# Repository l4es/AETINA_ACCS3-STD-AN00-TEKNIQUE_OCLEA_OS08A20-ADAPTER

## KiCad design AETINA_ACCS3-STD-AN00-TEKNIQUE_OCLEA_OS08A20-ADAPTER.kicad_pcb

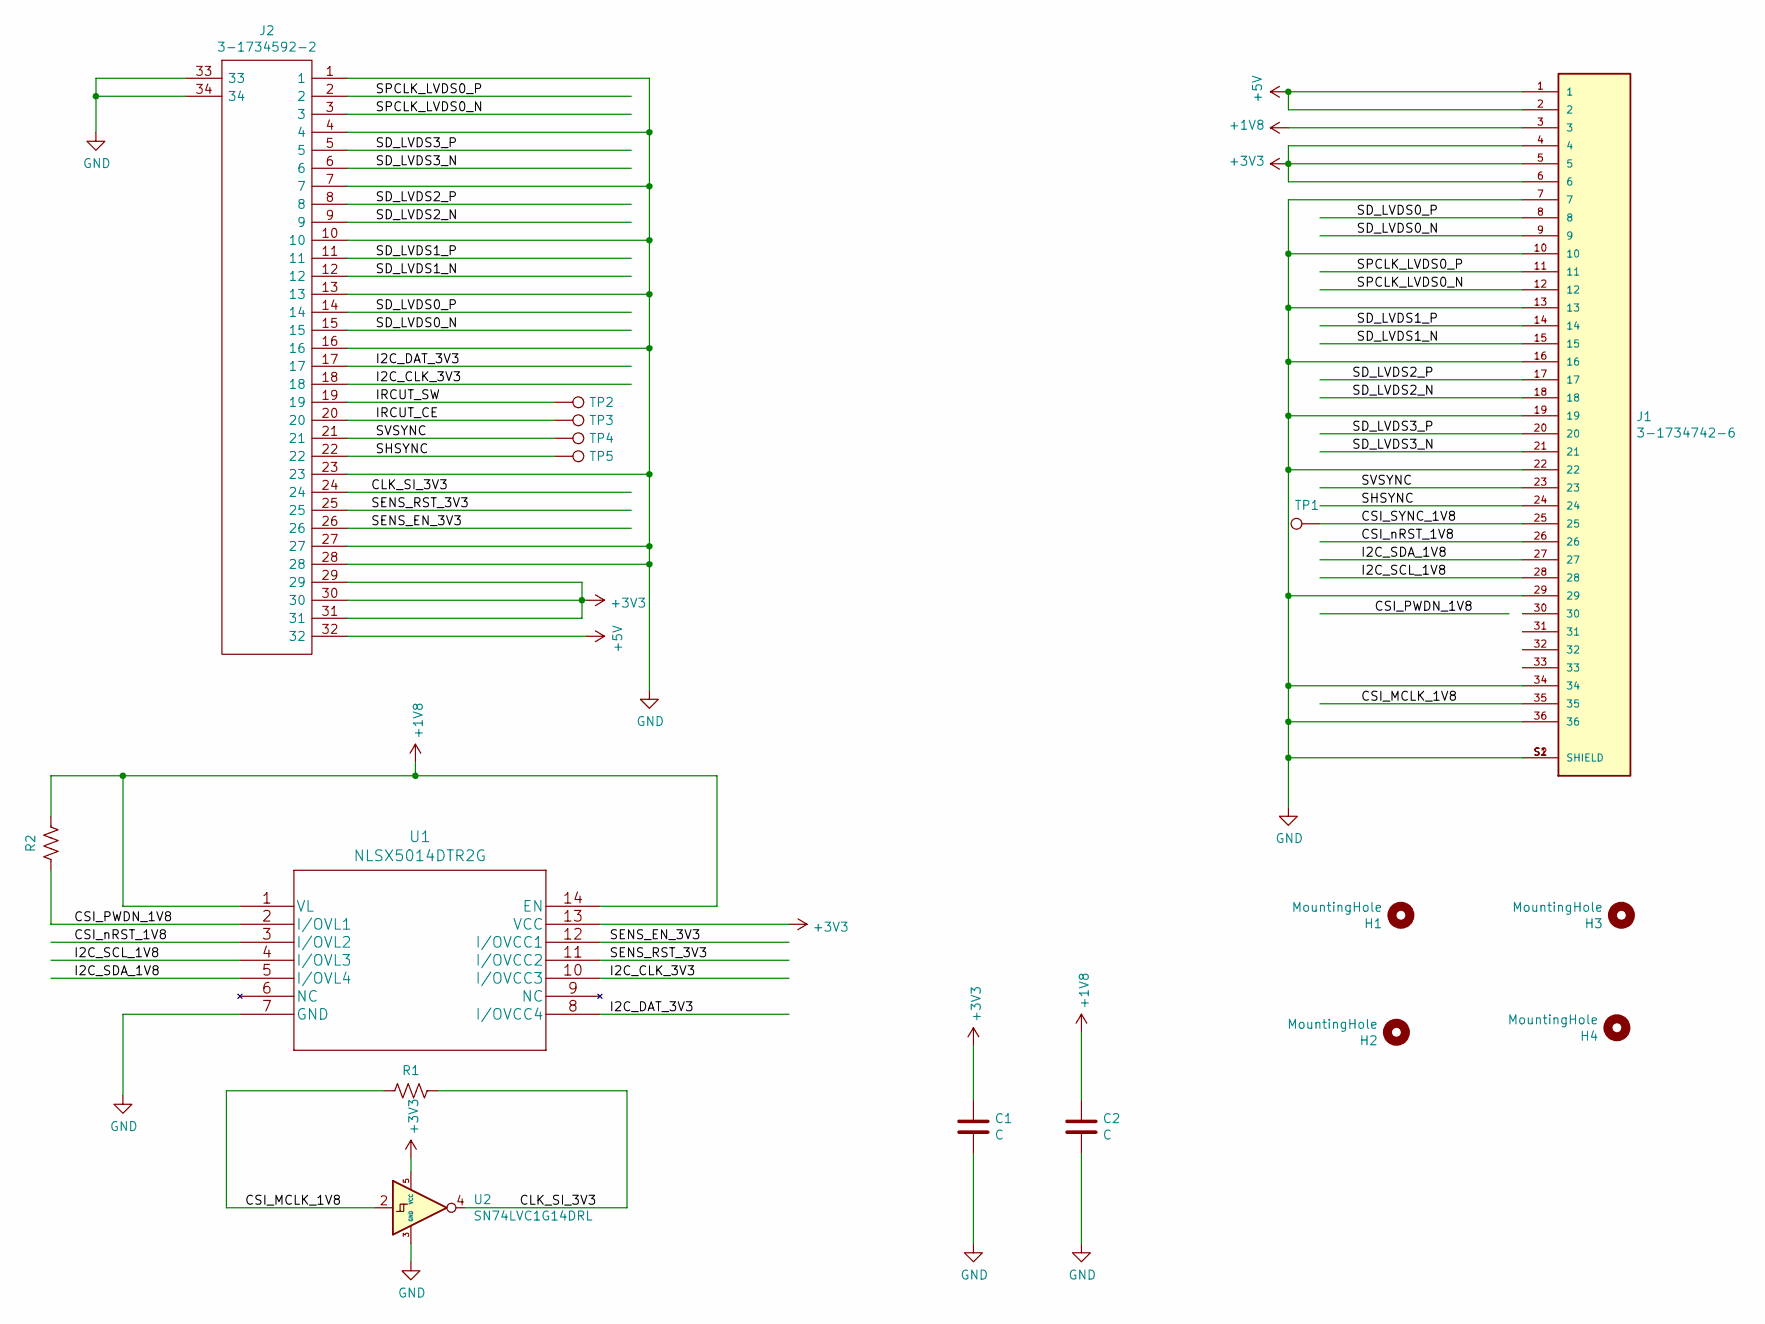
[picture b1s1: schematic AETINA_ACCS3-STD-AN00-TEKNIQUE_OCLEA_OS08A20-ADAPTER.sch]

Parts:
C1, C2: C; C_0603_1608Metric_Pad1.08x0.95mm_HandSolder
H1, H2, H3, H4: MountingHole; MountingHole_2.2mm_M2_Pad
J1: 3-1734742-6; TE_3-1734742-6; PARTREV P
J2: 3-1734592-2; 317345922; Manufacturer_Part_Number 3-1734592-2; Mouser Part Number 571-3-1734592-2
R1, R2: R_US; R_0805_2012Metric_Pad1.20x1.40mm_HandSolder
TP1, TP2, TP3, TP4, TP5: TestPoint; TestPoint_Pad_D1.0mm
U1: NLSX5014DTR2G
U2: SN74LVC1G14DRL; SOT-553

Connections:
+1V8: C2.1, J1.3, R2.1, U1.1 (VL), U1.14 (EN)
+3V3: C1.1, J1.4, J1.5, J1.6, J2.29, J2.30, J2.31, U1.13 (VCC), U2.5 (VCC)
+5V: J1.1, J1.2, J2.32
/CLK_SI_3V3: J2.24, R1.1, U2.4
/CSI_MCLK_1V8: J1.35, R1.2, U2.2
/CSI_PWDN_1V8: R2.2, U1.2 (I/OVL1)
/CSI_SYNC_1V8: J1.25, TP1.1
/CSI_nRST_1V8: J1.26, U1.3 (I/OVL2)
/I2C_CLK_3V3: J2.18, U1.10 (I/OVCC3)
/I2C_DAT_3V3: J2.17, U1.8 (I/OVCC4)
/I2C_SCL_1V8: J1.28, U1.4 (I/OVL3)
/I2C_SDA_1V8: J1.27, U1.5 (I/OVL4)
/IRCUT_CE: J2.20, TP3.1
/IRCUT_SW: J2.19, TP2.1
/SD_LVDS0_N: J1.9, J2.15
/SD_LVDS0_P: J1.8, J2.14
/SD_LVDS1_N: J1.15, J2.12
/SD_LVDS1_P: J1.14, J2.11
/SD_LVDS2_N: J1.18, J2.9
/SD_LVDS2_P: J1.17, J2.8
/SD_LVDS3_N: J1.21, J2.6
/SD_LVDS3_P: J1.20, J2.5
/SENS_EN_3V3: J2.26, U1.12 (I/OVCC1)
/SENS_RST_3V3: J2.25, U1.11 (I/OVCC2)
/SHSYNC: J1.24, J2.22, TP5.1
/SPCLK_LVDS0_N: J1.12, J2.3
/SPCLK_LVDS0_P: J1.11, J2.2
/SVSYNC: J1.23, J2.21, TP4.1
GND: C1.2, C2.2, J1.7, J1.10, J1.13, J1.16, J1.19, J1.22, J1.29, J1.34, J1.36, J1.S1 (SHIELD), J1.S2 (SHIELD), J2.1, J2.4, J2.7, J2.10, J2.13, J2.16, J2.23, J2.27, J2.28, J2.33, J2.34, U1.7 (GND), U2.3 (GND)

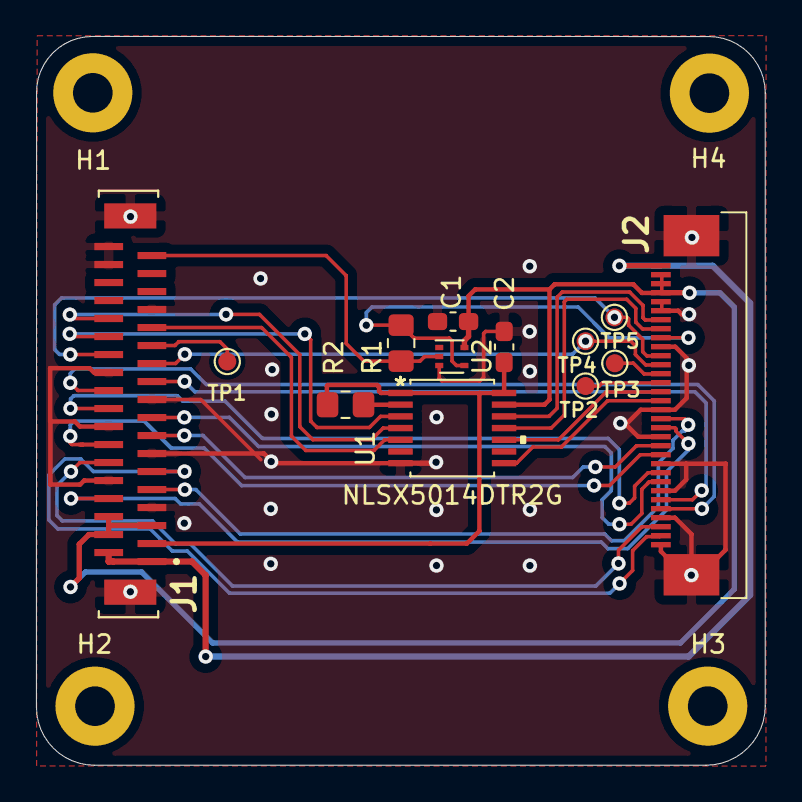
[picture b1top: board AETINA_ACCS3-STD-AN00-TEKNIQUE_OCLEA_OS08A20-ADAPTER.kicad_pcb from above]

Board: 2 copper layers, 40.5 x 40.5 mm, 17 parts (0 on the bottom side), 29 nets.

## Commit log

2021-08-08 Add first production release
2021-08-08 Rotate 3D model of J1 (3-1734742-6)

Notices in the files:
parts and their libraries:
Copyright 2021 Accelerated Designs. All rights reserved.
